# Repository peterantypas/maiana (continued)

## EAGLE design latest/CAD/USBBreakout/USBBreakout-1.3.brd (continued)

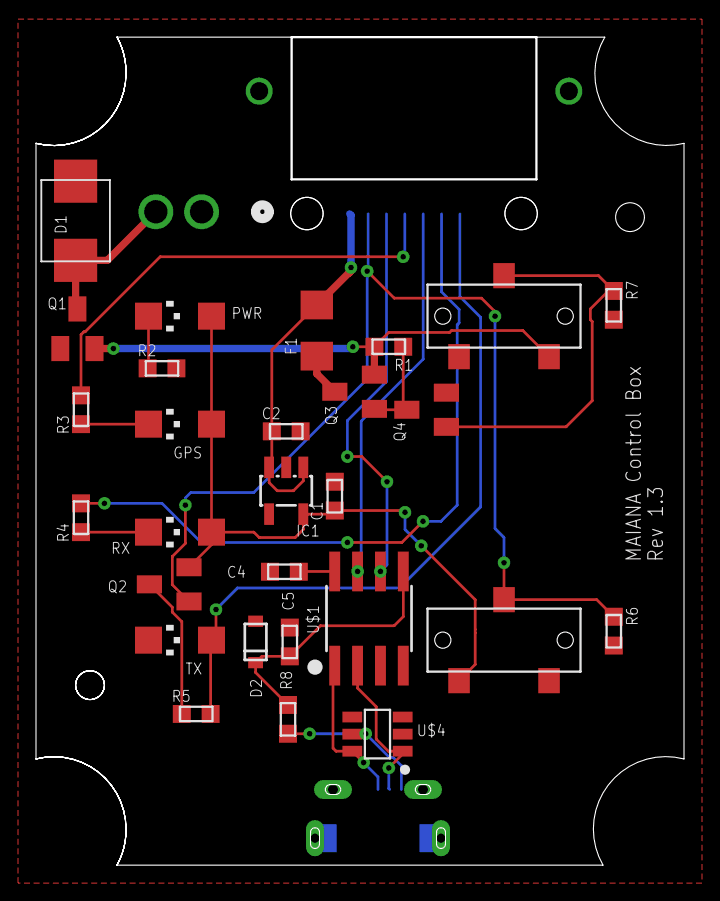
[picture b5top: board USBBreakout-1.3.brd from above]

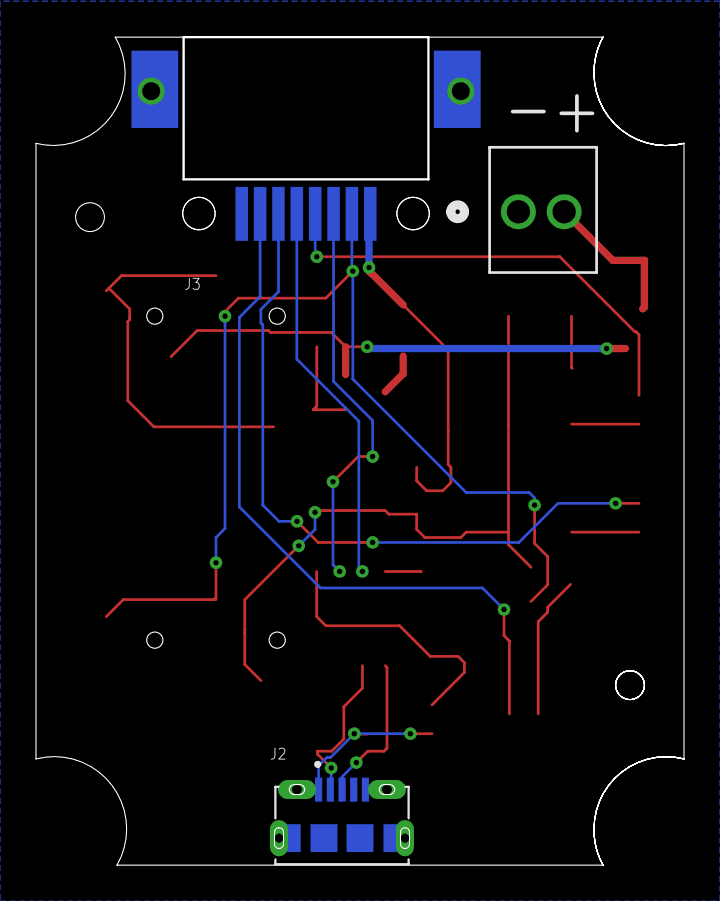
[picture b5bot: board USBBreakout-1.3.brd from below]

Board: 2 copper layers, 36.0 x 46.0 mm, 31 parts (3 on the bottom side), 23 nets.
